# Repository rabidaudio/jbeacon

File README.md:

# JBeacon

Bluetooth beacons and Android app to stop forgetting your friggin keys.

- [Android App](/app)
- [PCB](/jbeacon)
- [Case model](https://cad.onshape.com/documents/ece1ed75d93c6672117b46a9/w/23cbe3629f57f254decfda38/e/c40ef07a7db79b811c868a6b)

## Licenses

Source Code is [MIT](LICENSE).

Hardware designs are [CC By 4.0](https://creativecommons.org/licenses/by/4.0/)

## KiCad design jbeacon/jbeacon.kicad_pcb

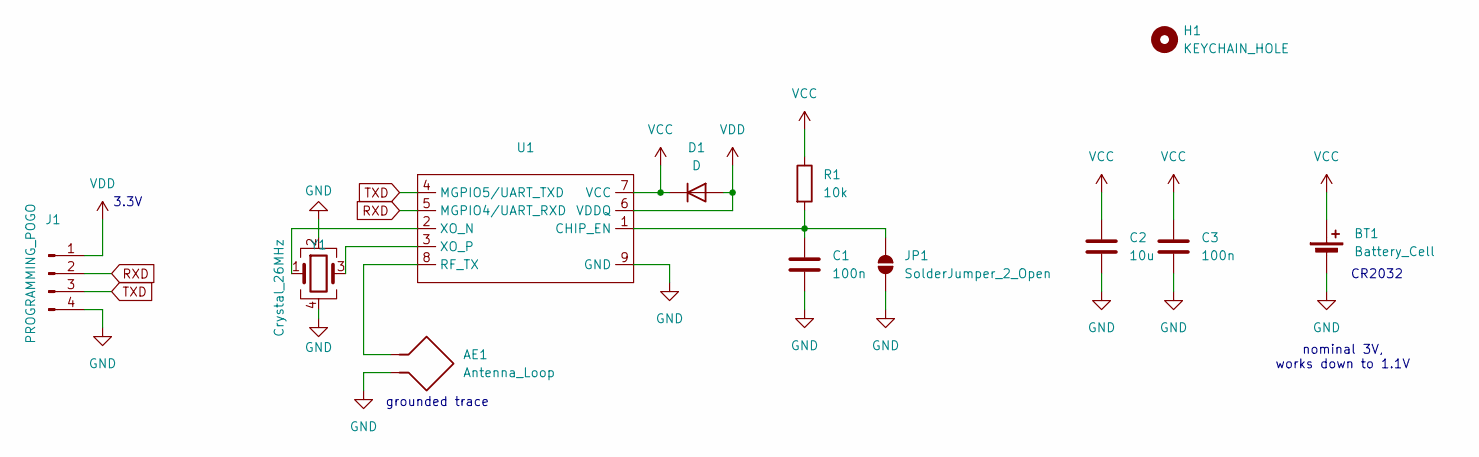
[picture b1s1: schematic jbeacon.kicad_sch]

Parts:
AE1: Antenna_Loop; rf_2.4ghz_pcb_antenna
BT1: Battery_Cell; BAT_BC-2003; Digikey_PN BC-2003-TR-CT-ND
C1, C3: 100n; C_0402_1005Metric; Digikey_PN 1276-1002-1-ND
C2: 10u; C_0402_1005Metric; Digikey_PN 1276-1451-1-ND
D1: D; D_0402_1005Metric; Digikey_PN 1N4148WL2-TPMSCT-ND
H1: KEYCHAIN_HOLE; MountingHole_3mm
J1: PROGRAMMING_POGO; pogo_4
JP1: SolderJumper_2_Open; SolderJumper-2_P1.3mm_Open_Pad1.0x1.5mm
R1: 10k; R_0402_1005Metric; Digikey_PN 311-10KJRCT-ND
U1: QFN-8_EP_2.5x2.5_Pitch0.5mm; Digikey_PN 3890-IN100-D1-R-YC1ICT-ND
Y1: Crystal_26MHz; OSC_XRCGB26M000F2P00R0; Digikey_PN 490-9764-1-ND

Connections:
GND: AE1.2, BT1.2 (-), C1.2, C2.2, C3.2, J1.4, JP1.1 (A), U1.9 (GND), Y1.2, Y1.4
unnamed: C1.1, JP1.2 (B), R1.2, U1.1 (CHIP_EN)
unnamed: AE1.1, U1.8 (RF_TX)
unnamed: U1.2 (XO_N), Y1.1
unnamed: U1.3 (XO_P), Y1.3
RXD: J1.2, U1.5 (MGPIO4/UART_RXD)
TXD: J1.3, U1.4 (MGPIO5/UART_TXD)
VCC: BT1.1 (+), C2.1, C3.1, D1.1 (K), R1.1, U1.7 (VCC)
VDD: D1.2 (A), J1.1, U1.6 (VDDQ)

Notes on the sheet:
3.3V
grounded trace
CR2032
nominal 3V, works down to 1.1V

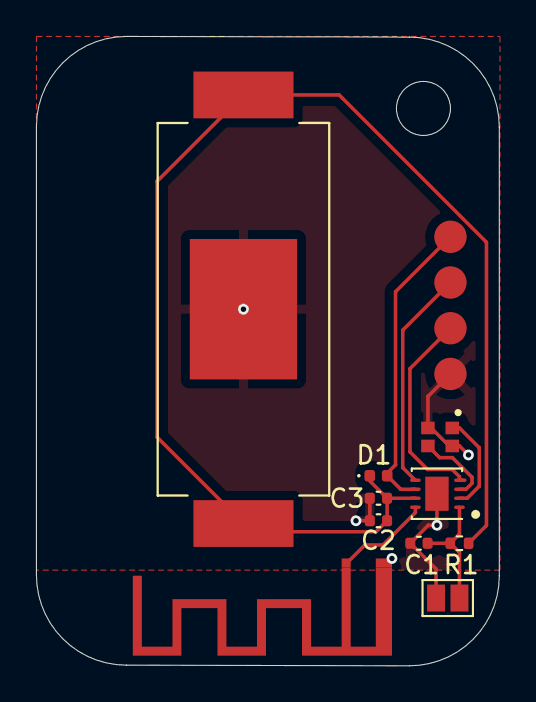
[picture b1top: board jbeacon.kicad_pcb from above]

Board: 2 copper layers, 25.7 x 35.0 mm, 12 parts (0 on the bottom side), 9 nets.

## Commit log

2024-12-13 install compose
2024-12-13 jetpack compose
2024-12-18 scanning for devices
2024-12-18 beacon manager class
2024-12-19 working UI
2024-12-24 start background implementation, fix caching
2024-12-24 add notifications
2024-12-24 try foreground service instead
2024-12-24 testing companion device
2024-12-28 Revert "testing companion device"
    This reverts commit 5826334c8fa2e39294f15a098563b7c059f815e0.
2024-12-28 Revert "try foreground service instead"
    This reverts commit 3c0d21f7ee72acac82651cd290f57bedf8055a42.
2024-12-28 fix background delivery results
2024-12-28 cleanup
2024-12-28 recover pcb
2024-12-28 more cleanup
2024-12-28 app icon
2024-12-28 case CAD
